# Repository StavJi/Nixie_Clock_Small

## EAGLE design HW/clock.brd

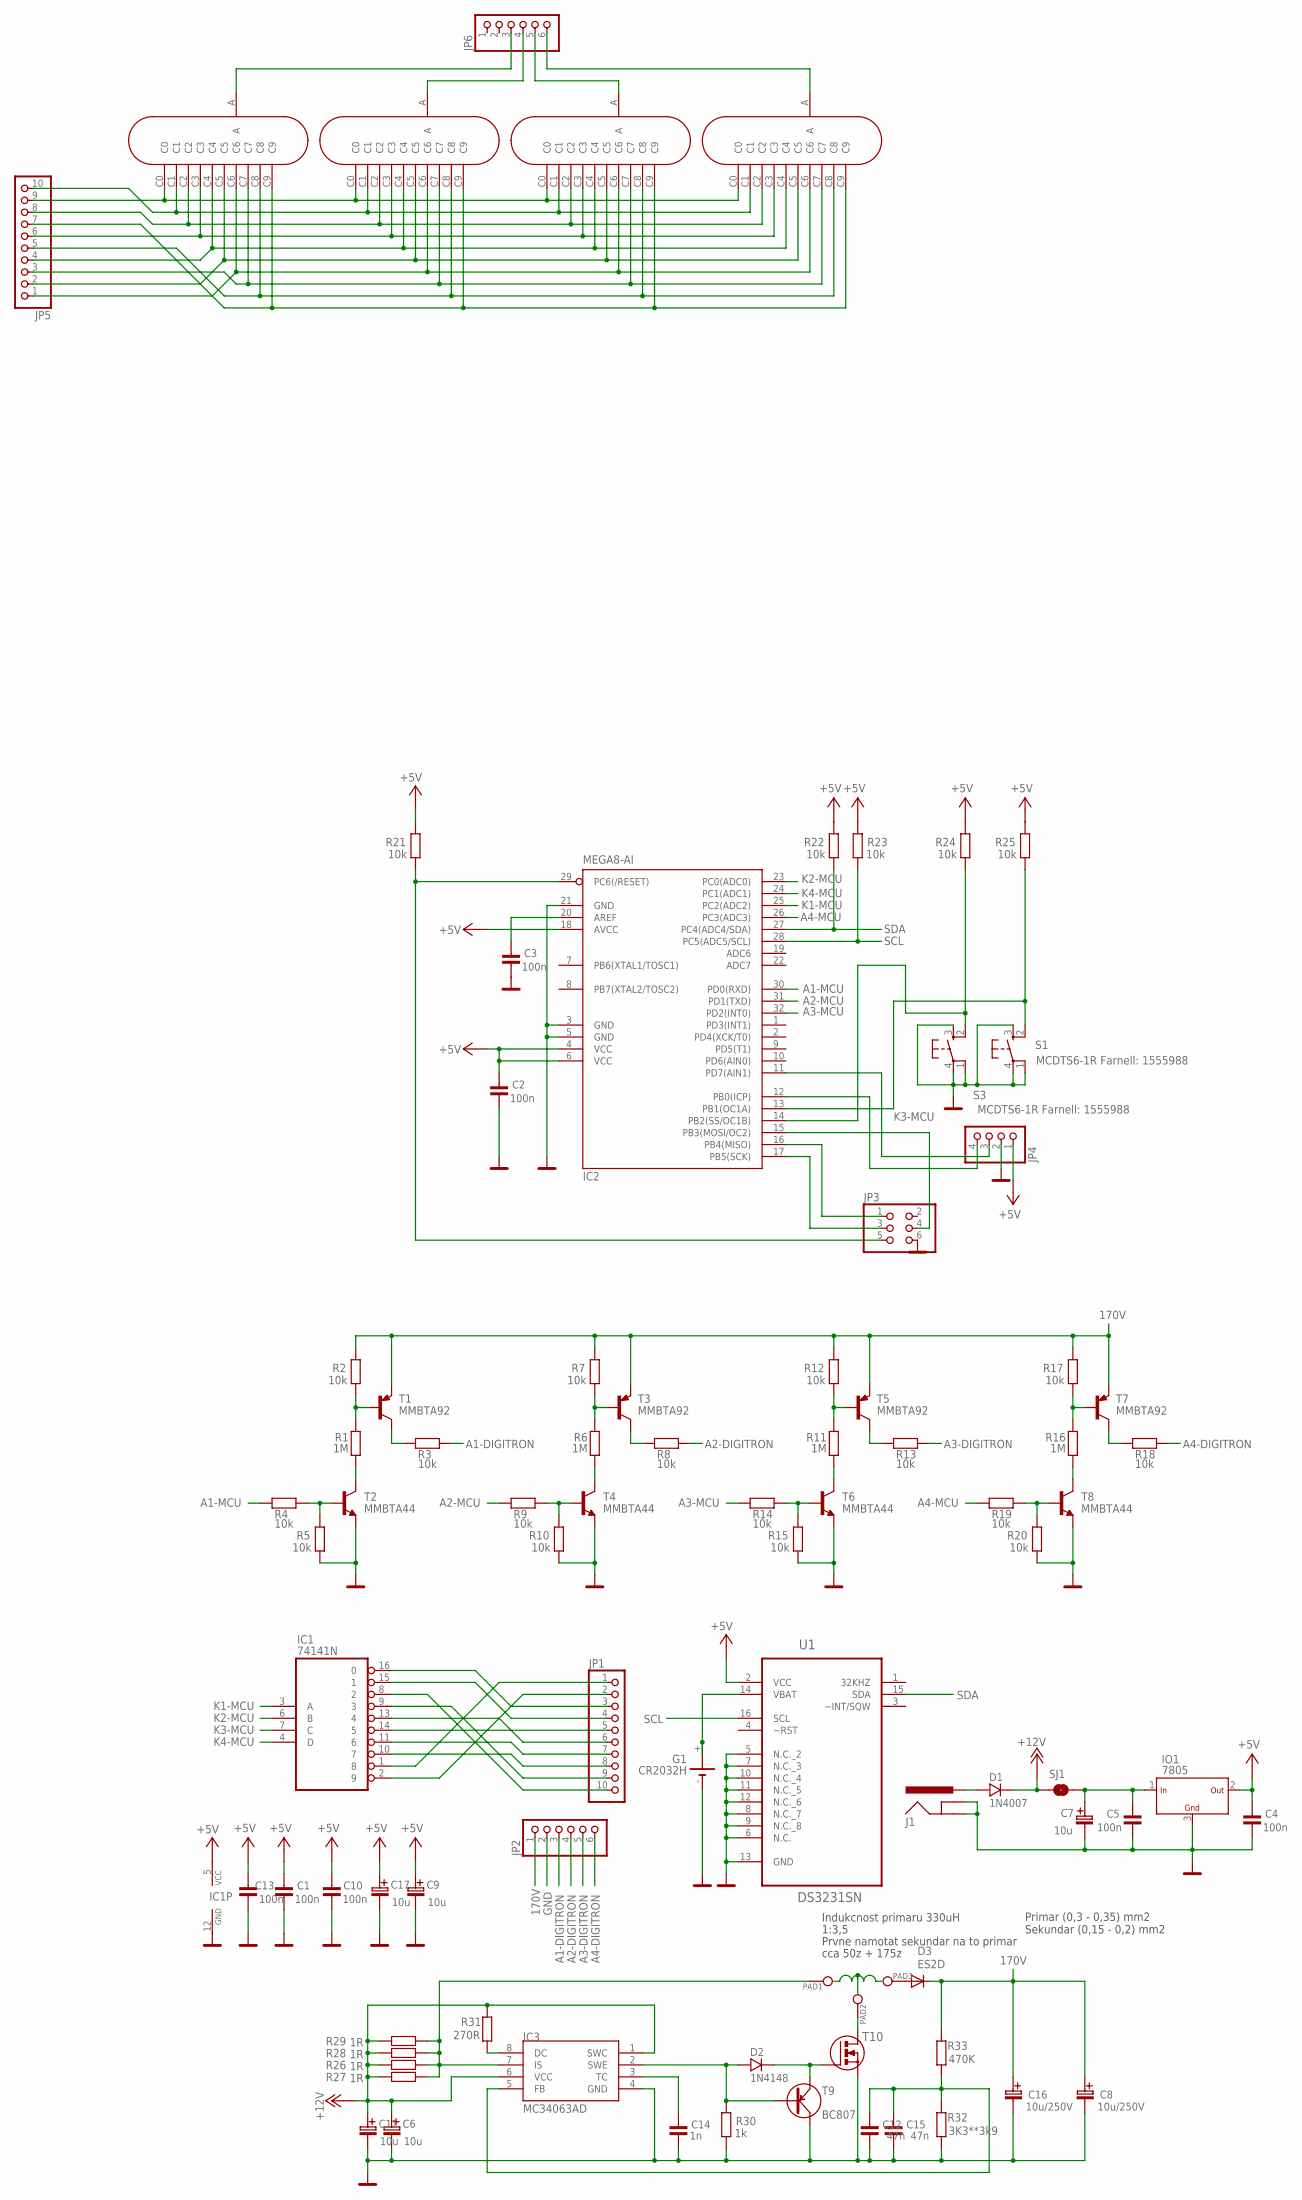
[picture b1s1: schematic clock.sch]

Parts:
C1, C2, C3, C4, C5, C10, C13: 100n; 0805
C6, C7, C9, C11, C17: 10u; A
C8, C16: 10u/250V; C_EL_5
C12, C15: 47n; 0805
C14: 1n; 0805
D1: 1N4007; SM-1
D2: 1N4148; SOD-80
D3: ES2D; SMB
E1, E2, E3, E4: Z573M
G1: CR2032H
IC1: 74141N; DIL16
IC2: MEGA8-AI; TQFP32-08
IC3: MC34063AD; SOIC8
IO1: 7805; D2PAK
J1: SPARKFUN_POWER_JACKSLT; SPARKFUN_POWER_JACK_SLOT
JP1, JP5: PINHD-1X10; 1X10
JP2, JP6: PINHD-1X6; 1X06
JP3: PINHD-2X3; 2X03
JP4: PINHD-1X4; 1X04
PAD1, PAD2, PAD3: PAD_1,8; PAD_1
R1, R6, R11, R16: 1M; 0805
R2, R4, R5, R7, R9, R10, R12, R14, R15, R17, R19, R20, R21, R22, R23, R24, R25: 10k; 0805
R3, R8, R13, R18: 10k; 1206
R26, R27, R28, R29: 1R; 1206
R30: 1k; 0805
R31: 270R; 0805
R32: 3K3**3k9; 0805
R33: 470K; 0805
S1, S3: MCDTS6-1R Farnell: 1555988; B3F-31XX
SJ1: SOLDERJUMPERNC; SJ-NC
T1, T3, T5, T7: MMBTA92; SOT23-BEC
T2, T4, T6, T8: MMBTA44; SOT23-BEC
T9: BC807; SOT-23
T10: SMD_NFET; D2PAK
U1: DS3231SN; SOIC127P1032X265-16N

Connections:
170V: C8.C+ (C_EL+), C16.C+ (C_EL+), D3.C, JP2.1, R2.2, R7.2, R12.2, R17.2, R33.1, T1.E, T3.E, T5.E, T7.E
+5V: C1.2, C2.2, C4.2, C9.+ (C_EL+), C10.2, C13.2, C17.+ (C_EL+), IC1.5 (VCC), IC2.4 (VCC), IC2.6 (VCC), IC2.18 (AVCC), IO1.2 (OUT), JP4.1, R21.2, R22.2, R23.2, R24.2, R25.2, U1.2 (VCC)
+12V: C6.+ (C_EL+), C11.+ (C_EL+), D1.K, IC3.1 (SWC), IC3.6 (VCC), R26.1, R27.1, R28.1, R29.1, R31.1, SJ1.1
A1-DIGITRON: JP2.3, R3.1
A1-MCU: IC2.30 (PD0(RXD)), R4.2
A2-DIGITRON: JP2.4, R8.1
A2-MCU: IC2.31 (PD1(TXD)), R9.2
A3-DIGITRON: JP2.5, R13.1
A3-MCU: IC2.32 (PD2(INT0)), R14.2
A4-DIGITRON: JP2.6, R18.1
A4-MCU: IC2.26 (PC3(ADC3)), R19.2
GND: C1.1, C2.1, C3.1, C4.1, C5.1, C6.- (C_EL-), C7.- (C_EL-), C8.C- (C_EL-), C9.- (C_EL-), C10.1, C11.- (C_EL-), C12.1, C13.1, C14.1, C15.1, C16.C- (C_EL-), C17.- (C_EL-), G1.-, IC1.12 (GND), IC2.3 (GND), IC2.5 (GND), IC2.21 (GND), IC3.4 (GND), IO1.3 (GND), J1.GND@1 (GNDBREAK), J1.GND@2 (GND), JP2.2, JP3.6, JP4.2, R5.1, R10.1, R15.1, R20.1, R30.1, R32.2, S1.1, S1.3 (S), S1.4, S3.1, S3.3 (S), S3.4, T2.E, T4.E, T6.E, T8.E, T9.3 (C), T10.2 (S), U1.5 (N.C._2), U1.6 (N.C.), U1.7 (N.C._3), U1.8 (N.C._7), U1.9 (N.C._8), U1.10 (N.C._4), U1.11 (N.C._5), U1.12 (N.C._6), U1.13 (GND)
K1-MCU: IC1.3 (A), IC2.25 (PC2(ADC2))
K2-MCU: IC1.6 (B), IC2.23 (PC0(ADC0))
K3-MCU: IC1.7 (C), IC2.15 (PB3(MOSI/OC2)), JP3.4
K4-MCU: IC1.4 (D), IC2.24 (PC1(ADC1))
unnamed: R1.2, R2.1, T1.B
unnamed: R3.2, T1.C
unnamed: R6.2, R7.1, T3.B
unnamed: R1.1, T2.C
unnamed: R4.1, R5.2, T2.B
unnamed: R8.2, T3.C
unnamed: R6.1, T4.C
unnamed: R9.1, R10.2, T4.B
unnamed: R11.2, R12.1, T5.B
unnamed: R13.2, T5.C
unnamed: R11.1, T6.C
unnamed: R14.1, R15.2, T6.B
unnamed: R16.2, R17.1, T7.B
unnamed: R18.2, T7.C
unnamed: R16.1, T8.C
unnamed: R19.1, R20.2, T8.B
unnamed: IC2.29 (PC6(/RESET)), JP3.5, R21.1
unnamed: IC2.14 (PB2(SS/OC1B)), R24.1, S3.2 (S1)
unnamed: C3.2, IC2.20 (AREF)
unnamed: D1.A, J1.PWR
unnamed: IC2.17 (PB5(SCK)), JP3.3
unnamed: G1.+, G1.+@1 (+), U1.14 (VBAT)
unnamed: IC2.13 (PB1(OC1A)), R25.1, S1.2 (S1)
unnamed: IC3.7 (IS), PAD1.1, R26.2, R27.2, R28.2, R29.2
unnamed: C12.2, C15.2, IC3.5 (FB), R32.1, R33.2
unnamed: PAD2.1, T10.3 (D)
unnamed: D3.A, PAD3.1
unnamed: IC1.10 (7), JP1.8
unnamed: IC1.9 (3), JP1.9
unnamed: IC1.11 (6), JP1.7
unnamed: IC1.13 (4), JP1.6
unnamed: IC1.8 (2), JP1.10
unnamed: IC1.14 (5), JP1.5
unnamed: IC1.15 (1), JP1.4
unnamed: IC1.16 (0), JP1.3
unnamed: IC1.1 (8), JP1.1
unnamed: IC1.2 (9), JP1.2
unnamed: C14.2, IC3.3 (TC)
unnamed: D2.A, IC3.2 (SWE), R30.2, T9.1 (B)
unnamed: D2.K, T9.2 (E), T10.1 (G)
unnamed: IC3.8 (DC), R31.2
unnamed: IC2.11 (PD7(AIN1)), JP4.3
unnamed: C5.2, C7.+ (C_EL+), IO1.1 (IN), SJ1.2
unnamed: IC2.12 (PB0(ICP)), JP4.4
unnamed: E2.A, JP6.4
unnamed: E1.C0, E2.C0, E3.C0, E4.C0, JP5.9
unnamed: E1.C1, E2.C1, E3.C1, E4.C1, JP5.10
unnamed: E1.C2, E2.C2, E3.C2, E4.C2, JP5.8
unnamed: E1.C3, E2.C3, E3.C3, E4.C3, JP5.6
unnamed: E1.C4, E2.C4, E3.C4, E4.C4, JP5.4
unnamed: E1.C5, E2.C5, E3.C5, E4.C5, JP5.2
unnamed: E1.C6, E2.C6, E3.C6, E4.C6, JP5.1
unnamed: E1.C7, E2.C7, E3.C7, E4.C7, JP5.3
unnamed: E1.C8, E2.C8, E3.C8, E4.C8, JP5.5
unnamed: E1.C9, E2.C9, E3.C9, E4.C9, JP5.7
unnamed: E3.A, JP6.5
unnamed: E4.A, JP6.6
unnamed: E1.A, JP6.3
SCL: IC2.28 (PC5(ADC5/SCL)), R23.1, U1.16 (SCL)
SDA: IC2.27 (PC4(ADC4/SDA)), R22.1, U1.15 (SDA)
SDASASDA: IC2.16 (PB4(MISO)), JP3.1

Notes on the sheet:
Indukcnost primaru 330uH
1:3,5
Prvne namotat sekundar na to primar
cca 50z + 175z
Primar (0,3 - 0,35) mm2 Sekundar (0,15 - 0,2) mm2

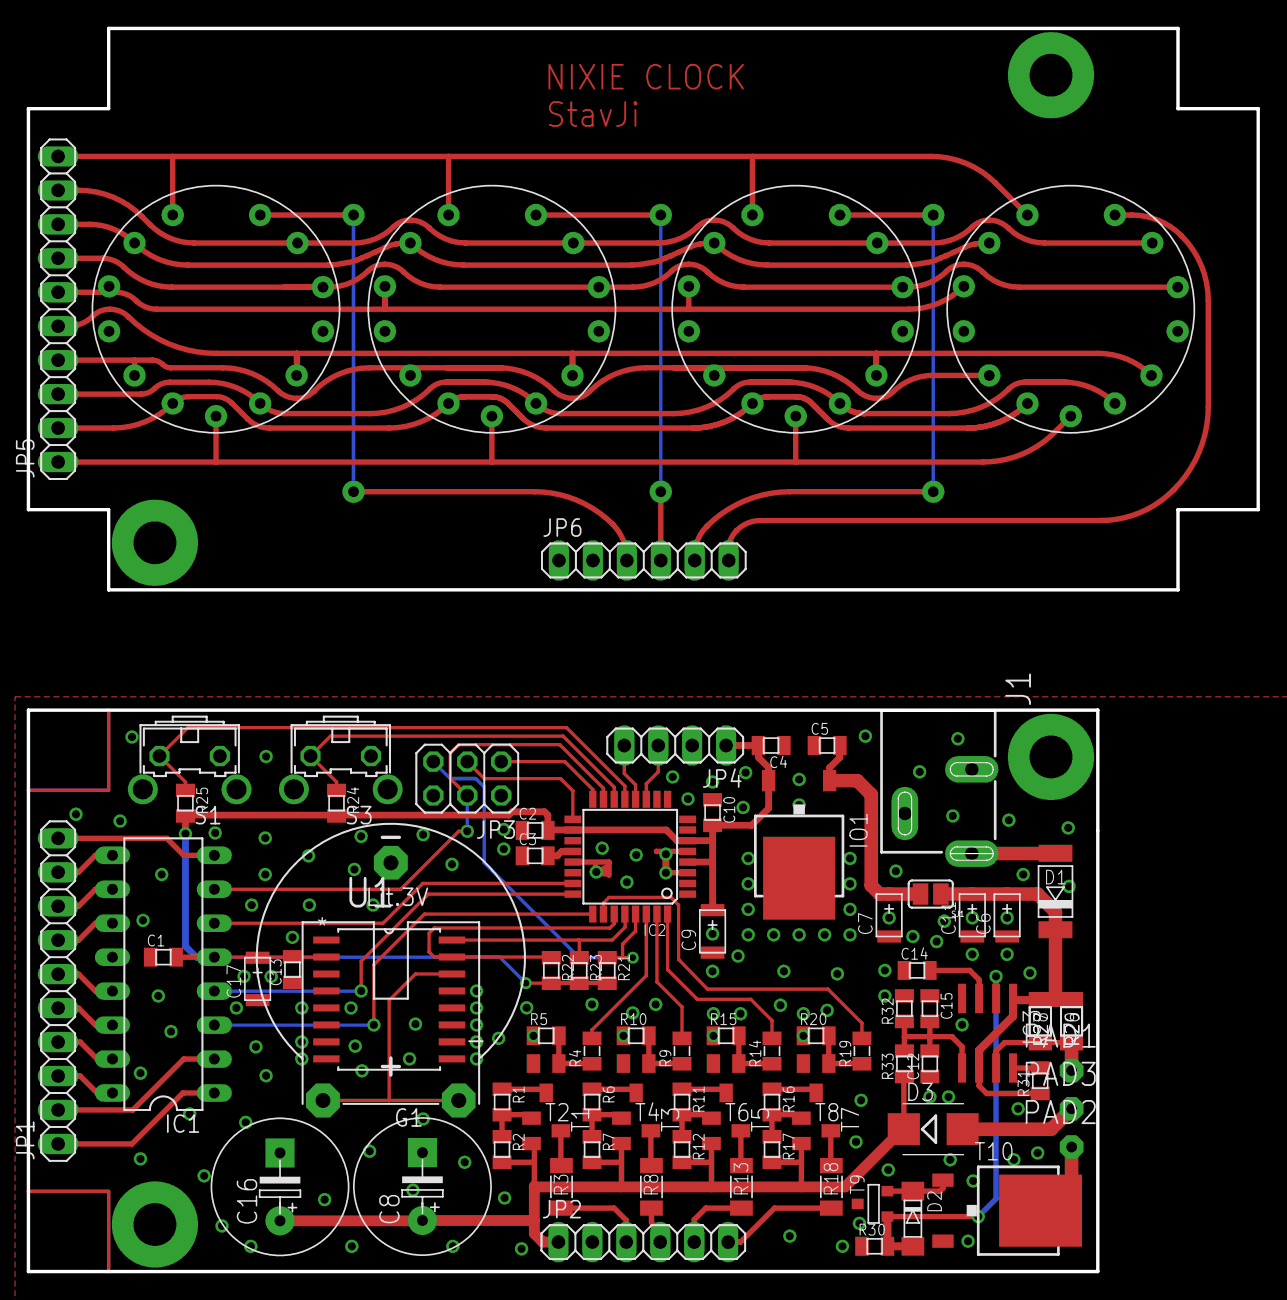
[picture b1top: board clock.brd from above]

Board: 2 copper layers, 92.0 x 93.0 mm, 86 parts (0 on the bottom side), 77 nets.

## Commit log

2021-03-15 added design files
2021-03-15 added photo of final clock
2021-03-15 add source file

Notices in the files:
parts and their libraries:
Copyright (C) PaJa 2001-2010
Copyright (C) PaJa 2001-2011
Copyright (C) PaJa 2003-2009
Copyright (C) PaJa 2009
Copyright (C) Jan 2007-2008
